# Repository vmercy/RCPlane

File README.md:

# Arduino Powered RC Plane <!-- omit in toc -->
* Author: Valentin Mercy
* Date: 21/11/2020
* Type: Arduino Project
* Languages: C/C++ Object Oriented

- [Software](#software)
  - [UML Diagram](#uml-diagram)
  - [Dependencies](#dependencies)
- [Electronics](#electronics)
  - [The Plane](#the-plane)
    - [Lipo back voltage measurement](#lipo-back-voltage-measurement)
  - [Remote Controller](#remote-controller)

## Software ##
### UML Diagram ###
### Dependencies ###
Some external Arduino librairies are used in this project. All of them can be installed from the Arduino IDE library manager.
* Adafruit_GFX
* SPI
* Wire
* Adafruit_SSD1306

## Electronics ##
Instead of using a ready-made RC kit with a standard controller, I decided to make my own electronics based on Arduino shields (Arduino Nano for the plane and Arduino Mega 2560 Pro Embed for the Radio Controller) communicating with NRF24L01 2.4 GHz long-range modules. As the space available for electronic stuff was very limited in my plane, I could not make a proper PCB. As to the RC controller, I designed a custom PCB with Autodesk Eagle software before ordering it on [JLCPCB](https://jlcpcb.com/).

### The Plane ###
#### Lipo back voltage measurement ####

### Remote Controller ###

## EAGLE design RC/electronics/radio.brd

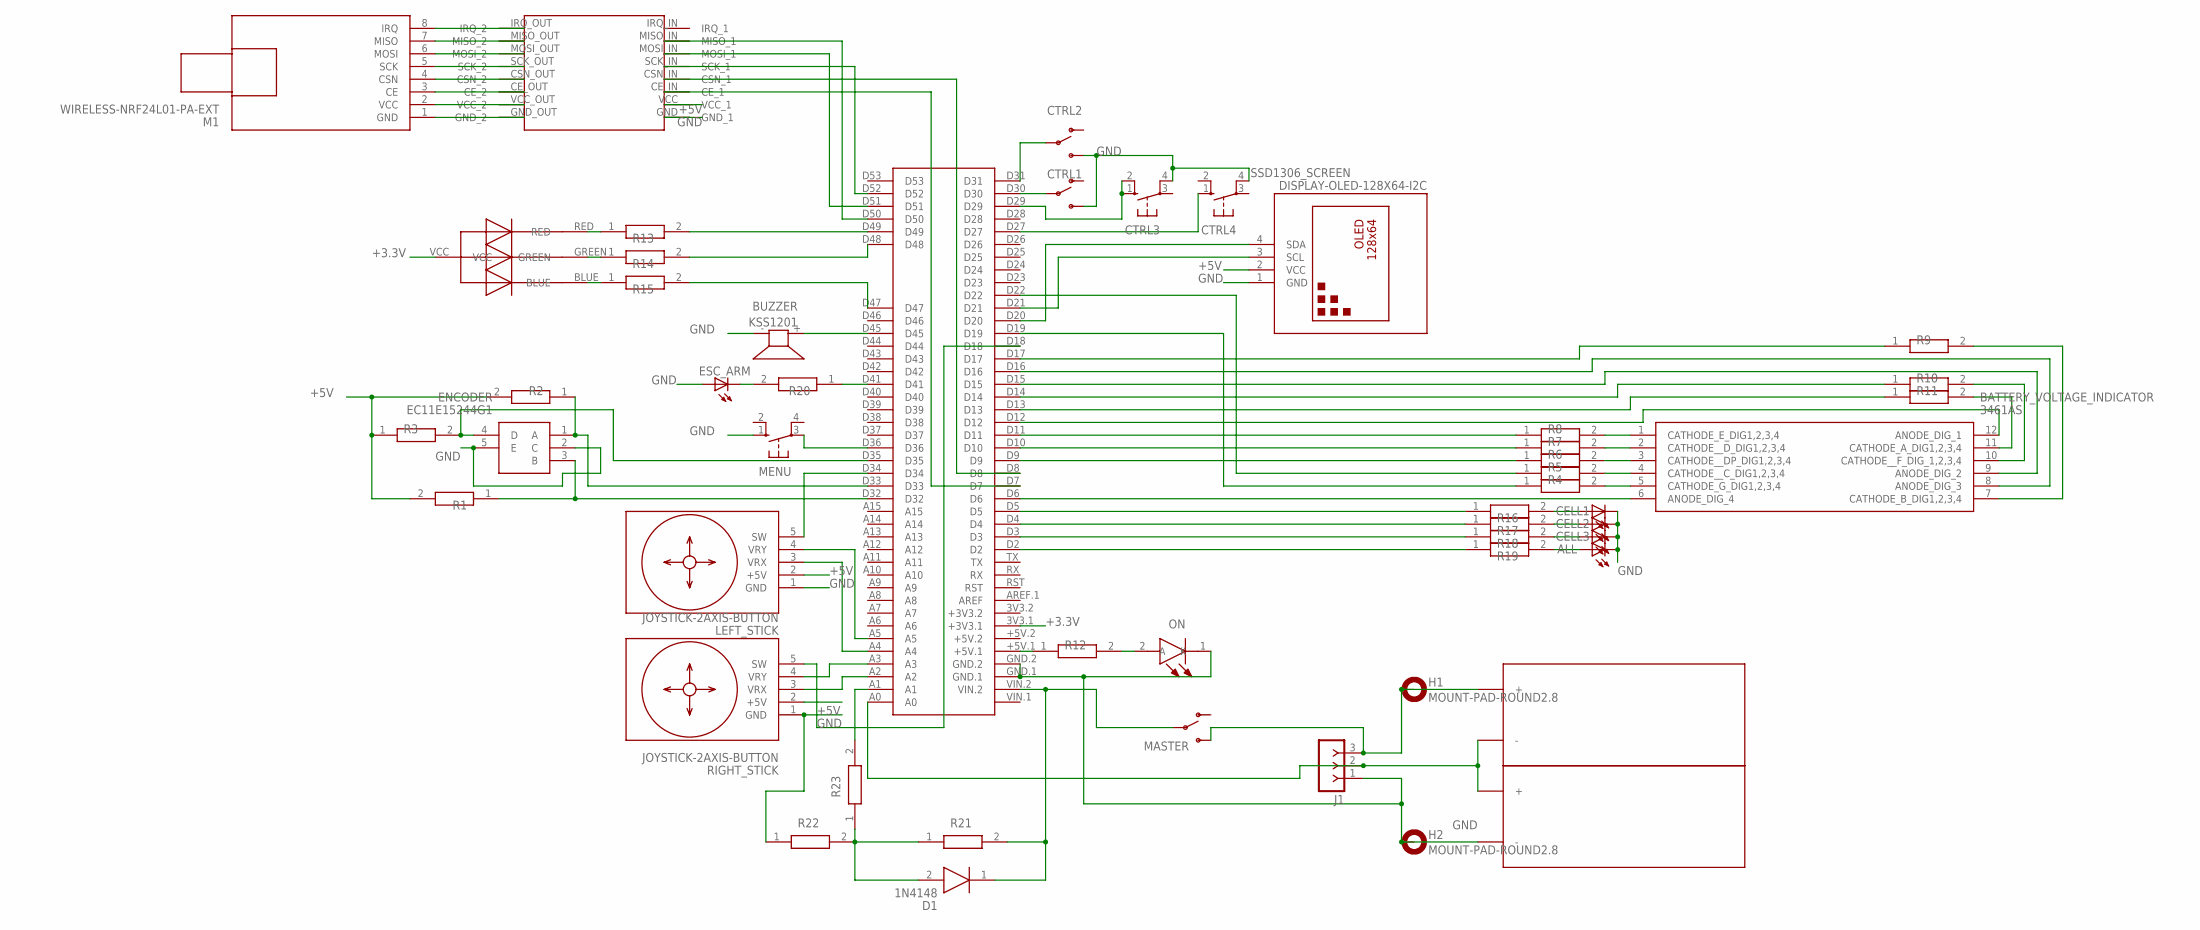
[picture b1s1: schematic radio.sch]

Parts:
ALL: LED3MM
BATTERY_VOLTAGE_INDICATOR: 3461AS; DIPS1016W45P254L3000H740Q12N
BUZZER: KSS1201
CELL1, CELL2, CELL3: LED3MM
CTRL1, CTRL2: SWITCH-SPDT-PTH-8.6X4.3MM; SWITCH_SPDT_8.6X4.3MM
CTRL3, CTRL4: 10-XX; B3F-10XX
D1: 1N4148; DIOAD1165W56L425D185
ENCODER: EC11E15244G1; EC11E1544505
ESC_ARM: LED3MM
GEAR: 5MMRGBLED; LED5MMRGB
H1, H2: MOUNT-PAD-ROUND2.8; 2,8-PAD
J1: F-1X03-SIP-100-32; SIP-100-03-32
LEFT_STICK: JOYSTICK-2AXIS-BUTTON
M1: WIRELESS-NRF24L01-PA-EXT
MASTER: SWITCH-SPDT-PTH-8.6X4.3MM; SWITCH_SPDT_8.6X4.3MM
MENU: 10-XX; B3F-10XX
ON: SSL-LX5093UWC_G; SSL-LX5093SGC/B
R1, R2, R3: CRCW120610K0FKEAHP; RESC3116X65N
R4, R5, R6, R7, R8, R9, R10, R11, R13, R14, R15: CR1206-FX-3300ELF; RESC3216X75N
R12: CRCW1206470RFKEA; RESC3216X60N
R16, R17, R18, R19, R20: CRG1206F150R; RESC3116X65N
R21, R22, R23: CRS1206-FX-1001ELF; RESC3116X65N
RIGHT_STICK: JOYSTICK-2AXIS-BUTTON
SSD1306_SCREEN: DISPLAY-OLED-128X64-I2C
U$3: YL-105-ADAPTER-NRF24L01; YL-105
U$8: MEGA2560_MIKRO

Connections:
+3.3V: GEAR.VCC, U$8.3V3.1 (+3V3.1)
+5V: LEFT_STICK.2 (+5V), R1.2, R2.2, R3.1, RIGHT_STICK.2 (+5V), SSD1306_SCREEN.2 (VCC), U$3.VCC (VCC_1)
GND: ALL.K (C), BUZZER.- (2), CELL1.K (C), CELL2.K (C), CELL3.K (C), CTRL1.3 (S), CTRL2.3 (S), CTRL3.4 (P1), CTRL4.4 (P1), ENCODER.2 (C), ENCODER.5 (E), ESC_ARM.A, H2.B2,8, J1.1, LEFT_STICK.1 (GND), MENU.1 (S), ON.1 (K), R22.1, RIGHT_STICK.1 (GND), SSD1306_SCREEN.1 (GND), U$3.GND (GND_1), U$8.GND.1, U$8.GND.2
unnamed: M1.1 (GND), U$3.GND_OUT (GND_2)
unnamed: M1.2 (VCC), U$3.VCC_OUT (VCC_2)
unnamed: M1.3 (CE), U$3.CE_OUT (CE_2)
unnamed: M1.4 (CSN), U$3.CSN_OUT (CSN_2)
unnamed: M1.5 (SCK), U$3.SCK_OUT (SCK_2)
unnamed: M1.6 (MOSI), U$3.MOSI_OUT (MOSI_2)
unnamed: M1.7 (MISO), U$3.MISO_OUT (MISO_2)
unnamed: M1.8 (IRQ), U$3.IRQ_OUT (IRQ_2)
unnamed: J1.2, U$8.A0
unnamed: R23.2, U$8.A1
unnamed: BATTERY_VOLTAGE_INDICATOR.6 (ANODE_DIG_4), U$8.D6
unnamed: BATTERY_VOLTAGE_INDICATOR.5 (CATHODE_G_DIG1,2,3,4), R6.2
unnamed: R6.1, U$8.D19
unnamed: BATTERY_VOLTAGE_INDICATOR.4 (CATHODE__C_DIG1,2,3,4), R5.2
unnamed: R5.1, U$8.D22
unnamed: R4.1, U$8.D9
unnamed: R7.1, U$8.D10
unnamed: R8.1, U$8.D11
unnamed: BATTERY_VOLTAGE_INDICATOR.1 (CATHODE_E_DIG1,2,3,4), R8.2
unnamed: BATTERY_VOLTAGE_INDICATOR.2 (CATHODE__D_DIG1,2,3,4), R7.2
unnamed: BATTERY_VOLTAGE_INDICATOR.3 (CATHODE__DP_DIG1,2,3,4), R4.2
unnamed: BATTERY_VOLTAGE_INDICATOR.12 (ANODE_DIG_1), U$8.D12
unnamed: R11.1, U$8.D13
unnamed: R10.1, U$8.D14
unnamed: BATTERY_VOLTAGE_INDICATOR.9 (ANODE_DIG_2), U$8.D15
unnamed: BATTERY_VOLTAGE_INDICATOR.8 (ANODE_DIG_3), U$8.D16
unnamed: R9.1, U$8.D17
unnamed: RIGHT_STICK.4 (VRY), U$8.A3
unnamed: RIGHT_STICK.3 (VRX), U$8.A2
unnamed: LEFT_STICK.3 (VRX), U$8.A4
unnamed: LEFT_STICK.4 (VRY), U$8.A5
unnamed: BATTERY_VOLTAGE_INDICATOR.7 (CATHODE_B_DIG1,2,3,4), R9.2
unnamed: BATTERY_VOLTAGE_INDICATOR.10 (CATHODE__F_DIG_1,2,3,4), R10.2
unnamed: BATTERY_VOLTAGE_INDICATOR.11 (CATHODE_A_DIG1,2,3,4), R11.2
unnamed: SSD1306_SCREEN.4 (SDA), U$8.D20
unnamed: SSD1306_SCREEN.3 (SCL), U$8.D21
unnamed: ENCODER.1 (A), R2.1, U$8.D33
unnamed: ENCODER.3 (B), R1.1, U$8.D32
unnamed: ENCODER.4 (D), R3.2, U$8.D35
unnamed: D1.2 (A), R21.1, R22.2, R23.1
unnamed: LEFT_STICK.5 (SW), U$8.D34
unnamed: CELL1.A, R16.2
unnamed: BUZZER.+ (1), U$8.D45
unnamed: RIGHT_STICK.5 (SW), U$8.D18
unnamed: CELL2.A, R17.2
unnamed: CELL3.A, R18.2
unnamed: ALL.A, R19.2
unnamed: MENU.3, U$8.D36
unnamed: ON.2 (A), R12.2
unnamed: CTRL1.2, U$8.D30
unnamed: CTRL2.2, U$8.D31
unnamed: CTRL3.1 (S), CTRL3.2 (S1), U$8.D29
unnamed: CTRL4.1 (S), U$8.D27
unnamed: R12.1, U$8.+5V.1
unnamed: GEAR.RED, R13.1
unnamed: GEAR.GREEN, R14.1
unnamed: GEAR.BLUE, R15.1
unnamed: R13.2, U$8.D49
unnamed: R14.2, U$8.D48
unnamed: R15.2, U$8.D47
unnamed: R16.1, U$8.D5
unnamed: R17.1, U$8.D4
unnamed: R18.1, U$8.D3
unnamed: R19.1, U$8.D2
unnamed: U$3.MISO_IN (MISO_1), U$8.D50
unnamed: U$3.MOSI_IN (MOSI_1), U$8.D51
unnamed: U$3.SCK_IN (SCK_1), U$8.D52
unnamed: U$3.CSN_IN (CSN_1), U$8.D8
unnamed: U$3.CE_IN (CE_1), U$8.D7
unnamed: R20.1, U$8.D41
unnamed: ESC_ARM.K (C), R20.2
VIN: H1.B2,8, J1.3, MASTER.3 (S)
VIN_SW: D1.1 (K), MASTER.2, R21.2, U$8.VIN.2

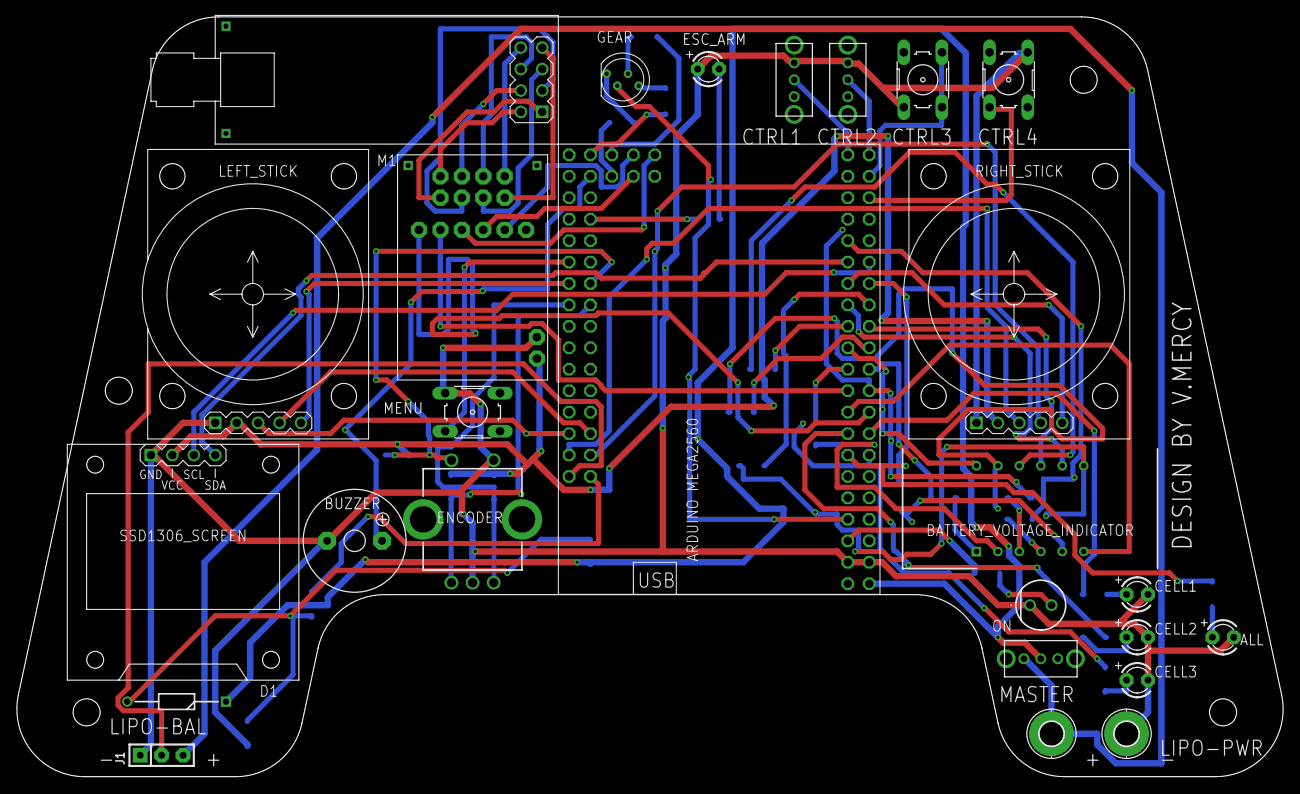
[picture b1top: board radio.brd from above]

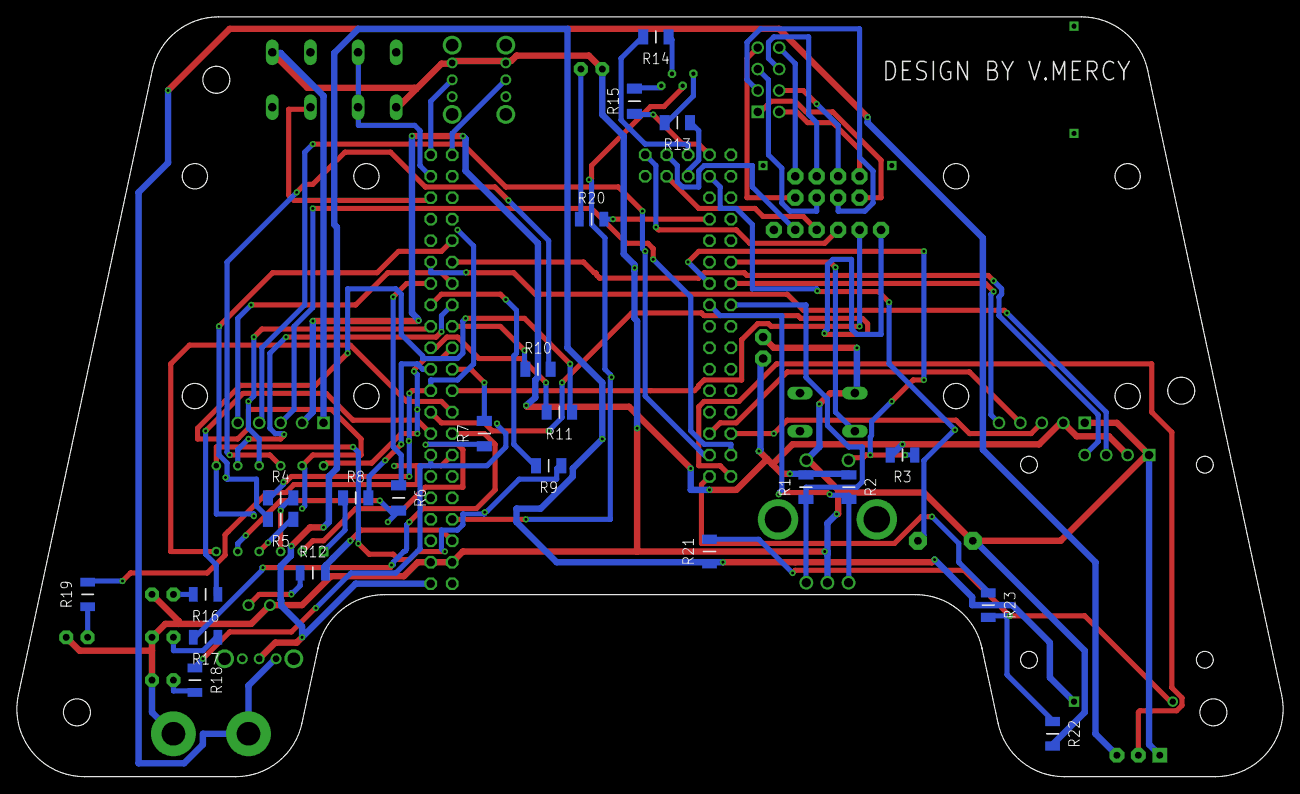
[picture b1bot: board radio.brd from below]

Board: 2 copper layers, 150.0 x 90.0 mm, 49 parts (23 on the bottom side), 76 nets.

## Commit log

2020-11-21 added README.md
2020-11-21 created component classes
2020-11-22 changed battery resistance array format
2020-11-22 implemented battery level measurement
2020-11-22 fixed typo mistakes
2020-11-23 aileron class working
2020-11-24 fixed battery class and added doc
2020-11-24 battery class working
2020-11-24 added Battery::print method
2020-11-25 ready to test battery time
2020-11-25 started implementation of RC objects
2020-11-26 added sampling to read analog values
2020-11-26 find max motor speed
2020-11-26 battery lifetime test
2020-11-26 button and joystick class working
2020-11-27 first check of RC classes
2020-11-27 separated vscode workspaces
2020-11-28 all RC devices are working well
2020-11-28 implemented all RC components classes and tests
2020-12-03 added startup bitmap to display on main lcd screen
2020-12-09 added rudder and made a ready-to-test version with controller incming frames
2020-12-09 deleted unused variables
2020-12-10 first test
2020-12-15 radio transmission is working outside class
2020-12-19 added todo
2020-12-19 attempt to resolve radio transmission problem
2020-12-21 changed NRF24L01 configuration
2020-12-21 added electronic schematics and control and settings classes
2020-12-21 disabled radio ack
2020-12-21 merge
2020-12-22 fixed const keyword missing in plane_battery_display class methods
2020-12-22 added settings and control classes
2020-12-24 renamed mathFunctions in snake-case (closing Issue 12) and templated homeMap function
2020-12-24 moved homeMap to math_functions.h
2020-12-24 added namespace around math functions
2020-12-24 updated RC doc
2020-12-25 documented remote_battery class
2020-12-25 added class doxygen tag above classes
2020-12-25 added class tag above plane classes
2020-12-25 updated doc
2020-12-25 updated plane doc and added doxyfile
2020-12-25 updated PlaneBatteryDisplay class
2020-12-25 moved some macros outside header.h
2020-12-25 corrected rgb led test method
2020-12-25 renamed PlaneBatteryDisplay in BatteryDisplaySet
2020-12-26 updated control class and replaced raw value 255 by UINT8_MAX
2020-12-27 updated Control class
2020-12-27 fixed cell indicators not updating on plane battery display

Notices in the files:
parts and their libraries:
diy-modules: Released under the Creative Commons Attribution 4.0 International License: http://creativecommons.org/licenses/by/4.0
SparkFun-Switches: Licensing: Creative Commons ShareAlike 4.0 International - https://creativecommons.org/licenses/by-sa/4.0
